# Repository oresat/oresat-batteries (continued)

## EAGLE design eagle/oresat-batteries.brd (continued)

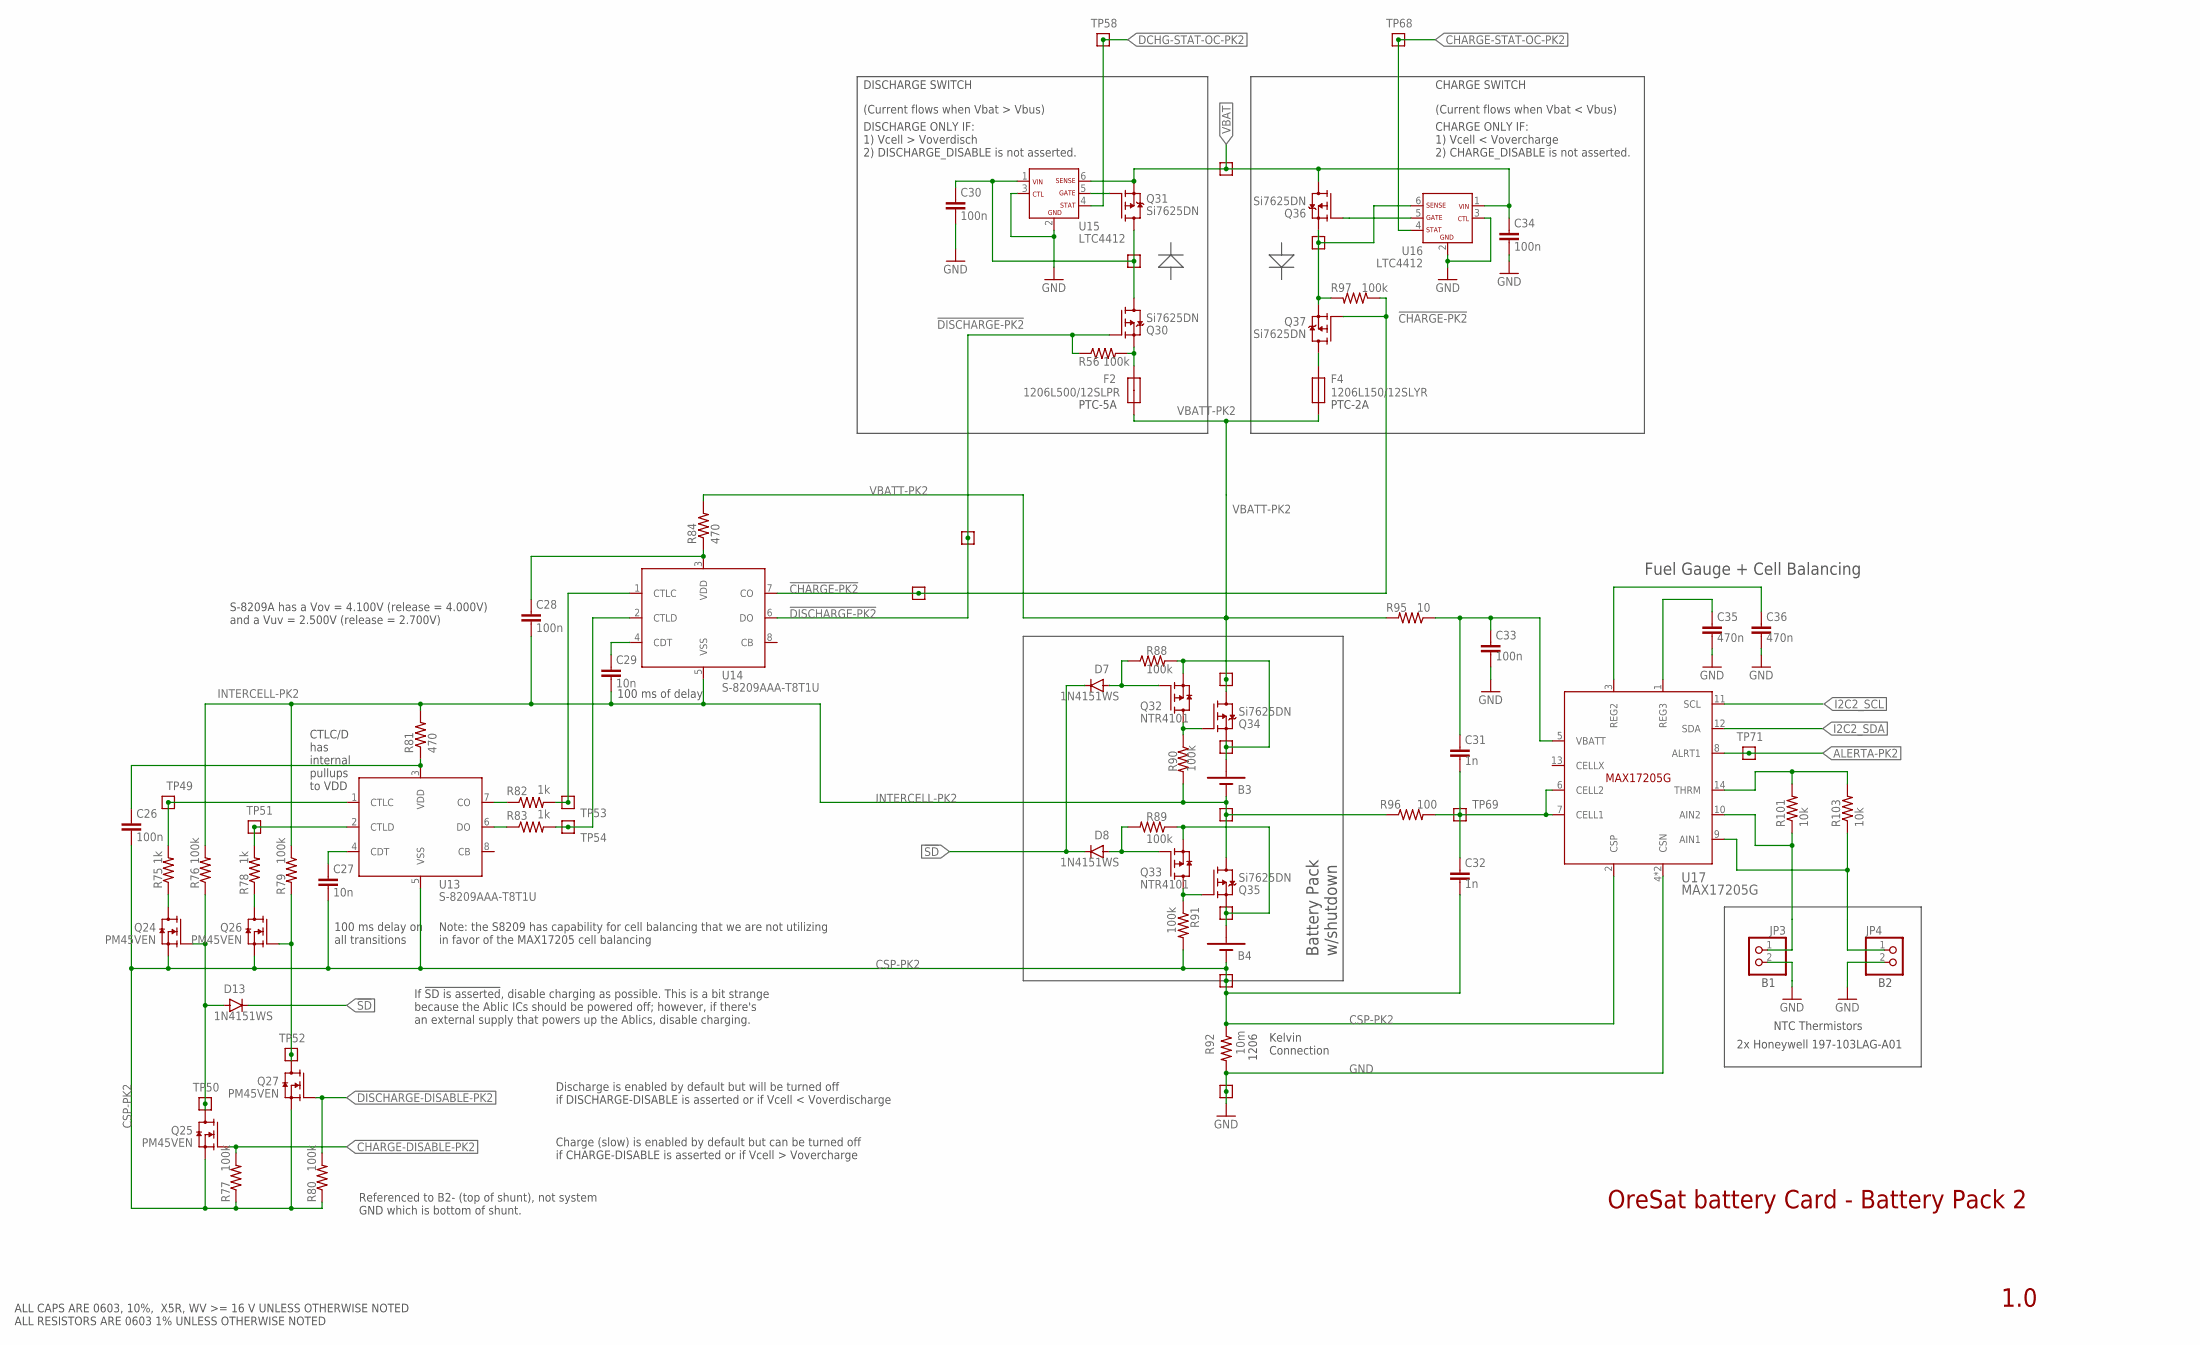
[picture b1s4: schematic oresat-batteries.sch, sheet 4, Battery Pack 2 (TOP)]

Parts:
B3, B4: B-18650-LI-BATTERY; 18650; MPN MH48285
C26, C28, C30, C33, C34: 100n; .0603-C-NOSILK; MPN C0603C104M4RACTU
C27, C29: 10n; .0603-C-NOSILK; MPN C0603C103M5RACTU
C31, C32: 1n; .0603-C-NOSILK; MPN CC0603KRX7R9BB102
C35, C36: 470n; .0603-C-NOSILK; MPN C0603C474K4PACTU
D7, D8, D13: 1N4151WS; SOD323-R; MPN 1N4151WS-E3-08
F2: 1206L500/12SLPR; 1206-C; MPN NANOSMD350LR-C-2
F4: 1206L150/12SLYR; 1206-C; MPN NANOSMD350LR-C-2
JP3, JP4: PINHD-1X2; 1X02
Q24, Q25, Q26, Q27: PM45VEN; SOT23-3; MPN PMV45EN2R
Q30, Q31, Q34, Q35, Q36, Q37: Si7625DN; POWERPAK-1212-8; MPN SI7625DN-T1-GE3
Q32, Q33: NTR4101; SOT23-3; MPN NTR4101PT1G
R56, R97: 100k; .0603-C-NOSILK; MPN RR0816P-104-D
R75, R78, R82, R83: 1k; .0603-C-NOSILK; MPN RC0603JR-071KL
R76, R79, R88, R89, R90, R91: 100k; .0603-C-NOSILK; MPN RC0603FR-071ML
R77, R80: 100k; .0603-C-NOSILK; MPN RC0603FR-0710KL
R81, R84: 470; .0603-C-NOSILK; MPN RC0603JR-07470RL
R92: 10m; 1206-C; MPN CSR1206-0R01F1
R95: 10; .0603-C-NOSILK; MPN RC0603FR-0710RL
R96: 100; .0603-C-NOSILK; MPN RC0603FR-07100RL
R101, R103: 10k; .0603-C-NOSILK; MPN RC0603FR-0710KL
TP24, TP49, TP50, TP51, TP52, TP53, TP54, TP55, TP56, TP58, TP59, TP61, TP62, TP63, TP64, TP65, TP66, TP67, TP68, TP69, TP71: TEST-POINT-LARGE-SQUARE; 1X01
U13, U14: S-8209AAA-T8T1U; TSSOP8; MPN S-8209AAA-T8T1U
U15, U16: LTC4412; SOT23-6; MPN LTC4412ES6#TRPBF
U17: MAX17205G; 21-0137I_T1433-2; MPN MAX17205G+T

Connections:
!CHARGE-PK2: Q37.4 (G), R97.1, TP56.1, U14.7 (CO)
!DISCHARGE-PK2: Q30.4 (G), R56.1, TP55.1, U14.6 (DO)
!SD: D7.C, D8.C, D13.C; also elsewhere on the board
AIN1-PK2: JP4.1, R103.1, U17.9 (AIN1)
AIN2-PK2: JP3.1, R101.1, U17.10 (AIN2)
ALERTA-PK2: TP71.1, U17.8 (ALRT1); also elsewhere on the board
CELL1-PK2: C31.2, C32.1, R96.2, TP69.1, U17.6 (CELL2), U17.7 (CELL1)
CHARGE-DISABLE-PK2: Q25.1 (G), R77.2; also elsewhere on the board
CHARGE-STAT-OC-PK2: TP68.1, U16.4 (STAT); also elsewhere on the board
CSP-PK2: B4.NEG-T (NEG), C26.2, C27.2, C32.2, Q24.2 (S), Q25.2 (S), Q26.2 (S), Q27.2 (S), R77.1, R80.1, R91.2, R92.1, TP65.1, U13.5 (VSS), U17.2 (CSP)
DCHG-STAT-OC-PK2: TP58.1, U15.4 (STAT); also elsewhere on the board
DISCHARGE-DISABLE-PK2: Q27.1 (G), R80.2; also elsewhere on the board
GND: C30.2, C33.2, C34.2, C35.2, C36.2, JP3.2, JP4.2, R92.2, TP66.1, U15.2 (GND), U15.3 (CTL), U16.2 (GND), U16.3 (CTL), U17.4 (CSN), U17.EP (CSN); also elsewhere on the board
I2C2_SCL: U17.11 (SCL); also elsewhere on the board
I2C2_SDA: U17.12 (SDA); also elsewhere on the board
INTERCELL-PK2: B3.NEG-T (NEG), C28.2, C29.2, Q35.5 (D), Q35.6 (D), Q35.7 (D), Q35.8 (D), Q35.PAD (D), R76.2, R79.1, R81.2, R90.2, R96.1, TP63.1, U14.5 (VSS)
unnamed: F4.1, Q37.5 (D), Q37.6 (D), Q37.7 (D), Q37.8 (D), Q37.PAD (D)
unnamed: Q36.1 (S), Q36.2 (S), Q36.3 (S), Q37.1 (S), Q37.2 (S), Q37.3 (S), R97.2, TP67.1, U16.6 (SENSE)
unnamed: F2.1, Q30.1 (S), Q30.2 (S), Q30.3 (S), R56.2
unnamed: R83.1, U13.6 (DO)
unnamed: R82.1, U13.7 (CO)
unnamed: R83.2, TP54.1, U14.2 (CTLD)
unnamed: R82.2, TP53.1, U14.1 (CTLC)
unnamed: R75.2, TP49.1, U13.1 (CTLC)
unnamed: C28.1, R84.1, U14.3 (VDD)
unnamed: C26.1, R81.1, U13.3 (VDD)
unnamed: C29.1, U14.4 (CDT)
unnamed: C27.1, U13.4 (CDT)
unnamed: Q31.4 (G), U15.5 (GATE)
unnamed: Q26.1 (G), Q27.3 (D), R79.2, TP52.1
unnamed: R78.2, TP51.1, U13.2 (CTLD)
unnamed: Q26.3 (D), R78.1
unnamed: Q36.4 (G), U16.5 (GATE)
unnamed: B3.POS-T (POS), Q32.2 (S), Q34.1 (S), Q34.2 (S), Q34.3 (S), R88.2, TP62.1
unnamed: Q33.3 (D), Q35.4 (G), R91.1
unnamed: D8.A, Q33.1 (G), R89.2
unnamed: B4.POS-T (POS), Q33.2 (S), Q35.1 (S), Q35.2 (S), Q35.3 (S), R89.1, TP64.1
unnamed: Q32.3 (D), Q34.4 (G), R90.1
unnamed: D7.A, Q32.1 (G), R88.1
unnamed: Q24.3 (D), R75.1
unnamed: D13.A, Q24.1 (G), Q25.3 (D), R76.1, TP50.1
REG2-PK2: C36.1, U17.3 (REG2)
REG3-PK2: C35.1, U17.1 (REG3)
THRM-PK2: R101.2, R103.2, U17.14 (THRM)
VBAT: C34.1, Q31.1 (S), Q31.2 (S), Q31.3 (S), Q36.5 (D), Q36.6 (D), Q36.7 (D), Q36.8 (D), Q36.PAD (D), TP59.1, U15.6 (SENSE), U16.1 (VIN); also elsewhere on the board
VBATT-F-PK2: C30.1, Q30.5 (D), Q30.6 (D), Q30.7 (D), Q30.8 (D), Q30.PAD (D), Q31.5 (D), Q31.6 (D), Q31.7 (D), Q31.8 (D), Q31.PAD (D), TP24.1, U15.1 (VIN)
VBATT-PK2: F2.2, F4.2, Q34.5 (D), Q34.6 (D), Q34.7 (D), Q34.8 (D), Q34.PAD (D), R84.2, R95.2, TP61.1
VBATT-PL2: C31.1, C33.1, R95.1, U17.5 (VBATT)

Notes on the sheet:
OreSat battery Card - Battery Pack 2
1.0
1206
NTC Thermistors
Battery Pack w/shutdown
Fuel Gauge + Cell Balancing
Note: the S8209 has capability for cell balancing that we are not utilizing in favor of the MAX17205 cell balancing
100 ms of delay
DISCHARGE SWITCH
(Current flows when Vbat > Vbus)
DISCHARGE ONLY IF: 1) Vcell > Voverdisch 2) DISCHARGE_DISABLE is not asserted.
CTLC/D has internal pullups to VDD
100 ms delay on all transitions
Discharge is enabled by default but will be turned off if DISCHARGE-DISABLE is asserted or if Vcell < Voverdischarge
Charge (slow) is enabled by default but can be turned off if CHARGE-DISABLE is asserted or if Vcell > Vovercharge
CHARGE SWITCH
(Current flows when Vbat < Vbus)
CHARGE ONLY IF: 1) Vcell < Vovercharge 2) CHARGE_DISABLE is not asserted.
Kelvin Connection
S-8209A has a Vov = 4.100V (release = 4.000V) and a Vuv = 2.500V (release = 2.700V)
Referenced to B2- (top of shunt), not system GND which is bottom of shunt.
ALL CAPS ARE 0603, 10%, X5R, WV >= 16 V UNLESS OTHERWISE NOTED ALL RESISTORS ARE 0603 1% UNLESS OTHERWISE NOTED
PTC-5A
PTC-2A
2x Honeywell 197-103LAG-A01
If !SD is asserted, disable charging as possible. This is a bit strange because the Ablic ICs should be powered off; however, if there's an external supply that powers up the Ablics, disable charging.

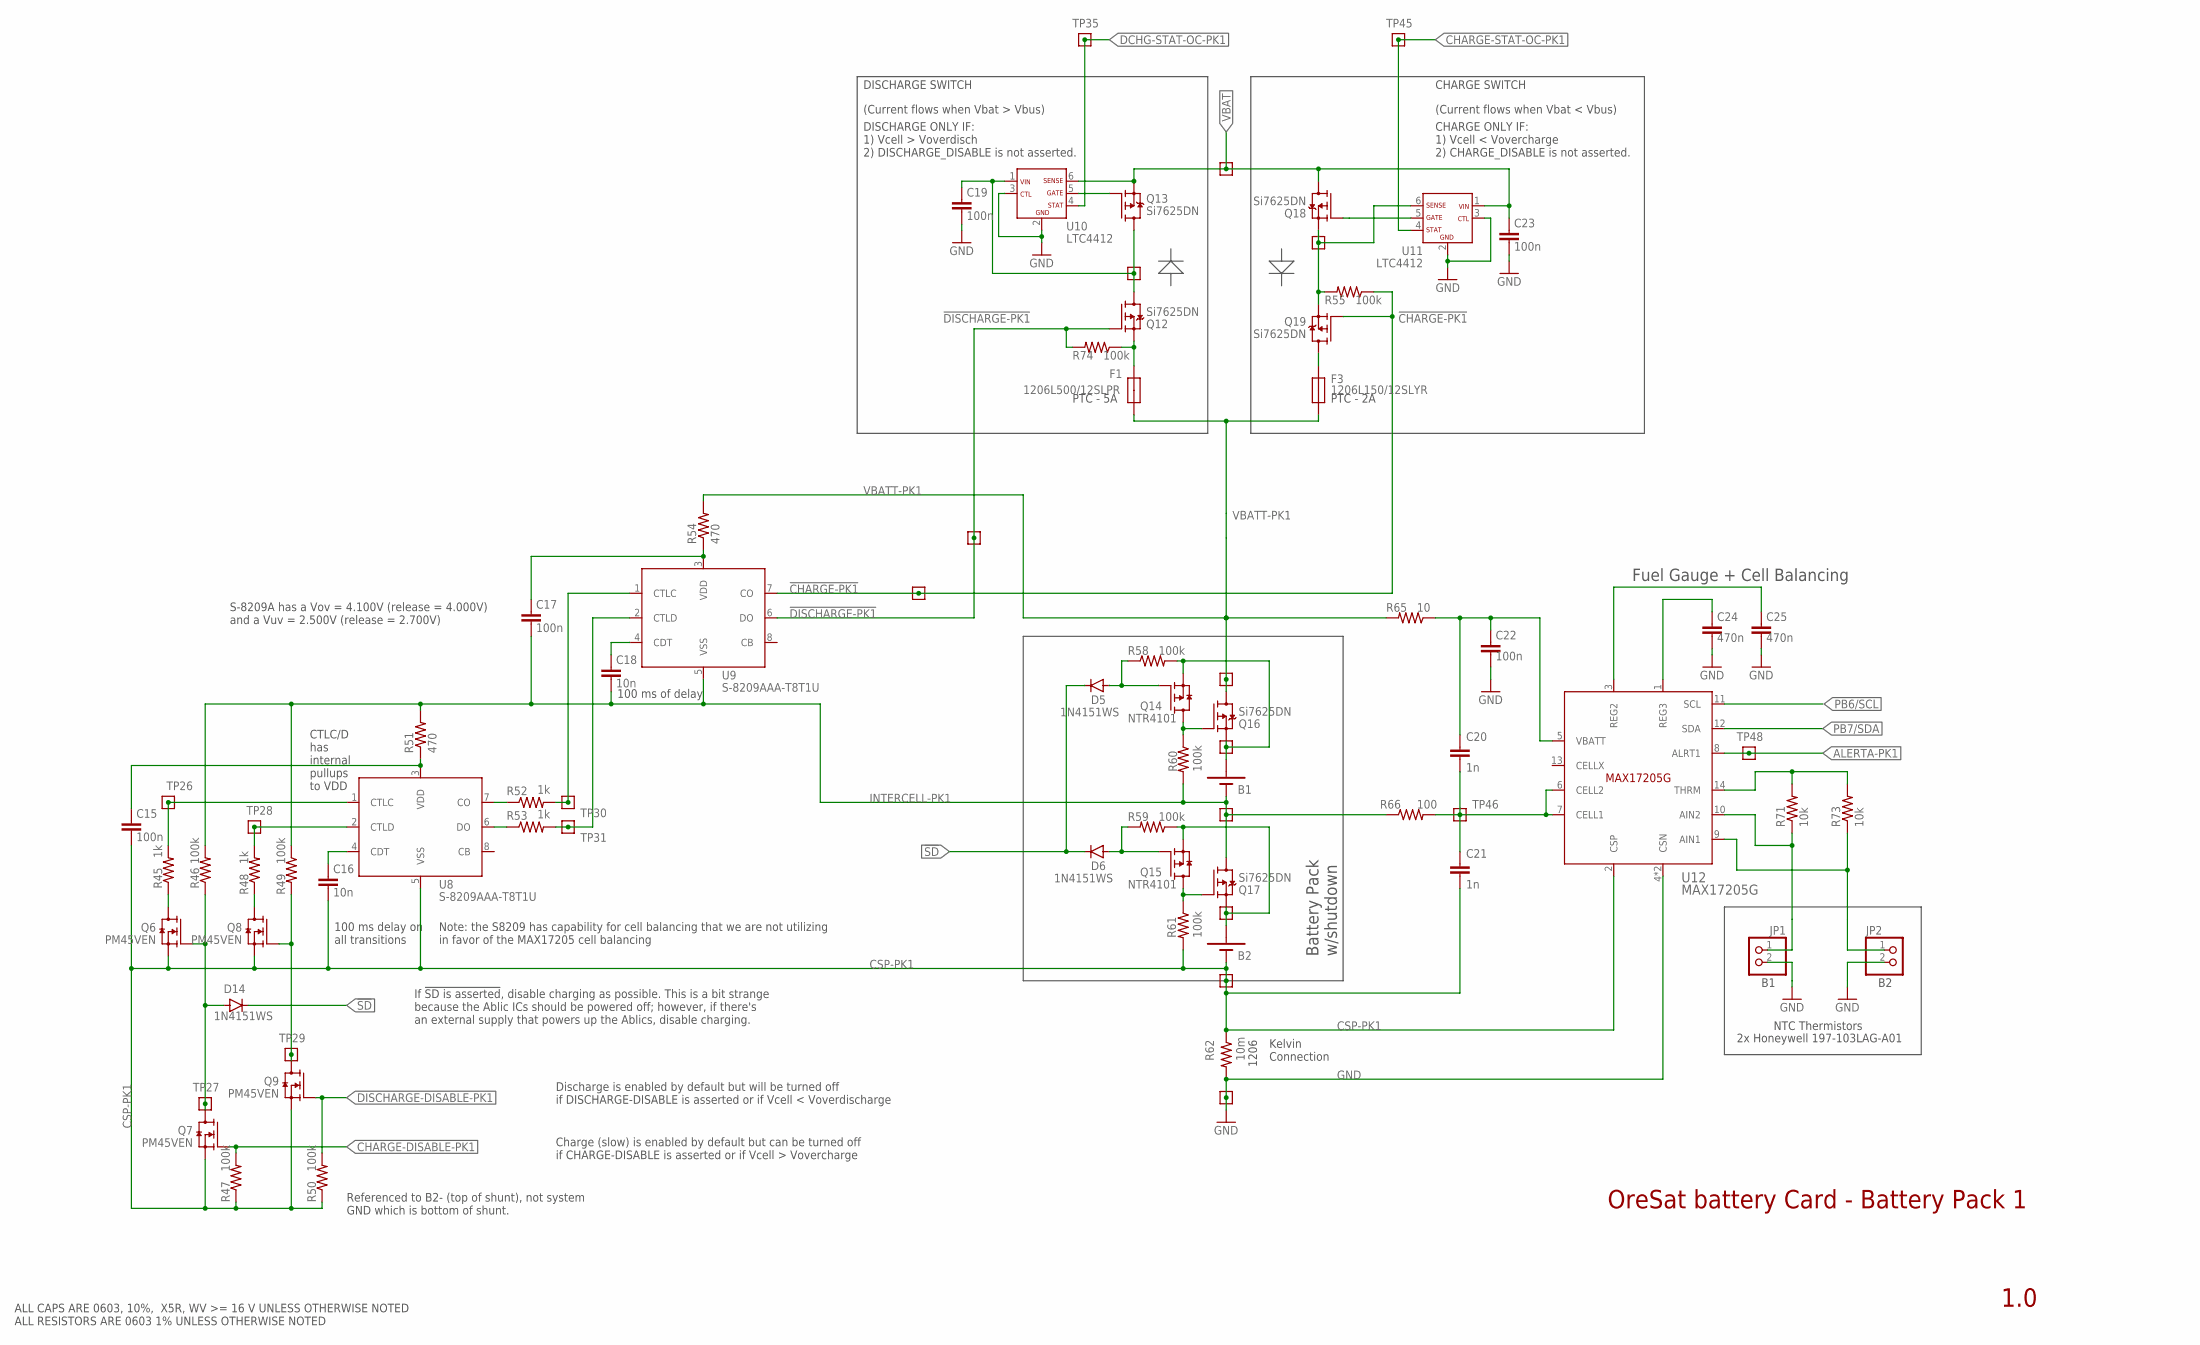
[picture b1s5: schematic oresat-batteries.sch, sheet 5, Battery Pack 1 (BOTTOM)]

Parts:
B1, B2: B-18650-LI-BATTERY; 18650; MPN MH48285
C15, C17, C19, C22, C23: 100n; .0603-C-NOSILK; MPN C0603C104M4RACTU
C16, C18: 10n; .0603-C-NOSILK; MPN C0603C103M5RACTU
C20, C21: 1n; .0603-C-NOSILK; MPN CC0603KRX7R9BB102
C24, C25: 470n; .0603-C-NOSILK; MPN C0603C474K4PACTU
D5, D6, D14: 1N4151WS; SOD323-R; MPN 1N4151WS-E3-08
F1: 1206L500/12SLPR; 1206-C; MPN NANOSMD350LR-C-2
F3: 1206L150/12SLYR; 1206-C; MPN NANOSMD350LR-C-2
JP1, JP2: PINHD-1X2; 1X02
Q6, Q7, Q8, Q9: PM45VEN; SOT23-3; MPN PMV45EN2R
Q12, Q13, Q16, Q17, Q18, Q19: Si7625DN; POWERPAK-1212-8; MPN SI7625DN-T1-GE3
Q14, Q15: NTR4101; SOT23-3; MPN NTR4101PT1G
R45, R48, R52, R53: 1k; .0603-C-NOSILK; MPN 311-1.0KGRCT-ND
R46, R49, R58, R59, R60, R61: 100k; .0603-C-NOSILK; MPN RC0603FR-071ML
R47, R50: 100k; .0603-C-NOSILK; MPN RC0603FR-0710KL
R51, R54: 470; .0603-C-NOSILK; MPN RC0603JR-07470RL
R55, R74: 100k; .0603-C-NOSILK; MPN RR0816P-104-D
R62: 10m; 1206-C; MPN CSR1206-0R01F1
R65: 10; .0603-C-NOSILK; MPN RC0603FR-0710RL
R66: 100; .0603-C-NOSILK; MPN RC0603FR-07100RL
R71, R73: 10k; .0603-C-NOSILK; MPN RC0603FR-0710KL
TP23, TP26, TP27, TP28, TP29, TP30, TP31, TP32, TP33, TP35, TP36, TP38, TP39, TP40, TP41, TP42, TP43, TP44, TP45, TP46, TP48: TEST-POINT-LARGE-SQUARE; 1X01
U8, U9: S-8209AAA-T8T1U; TSSOP8; MPN S-8209AAA-T8T1U
U10, U11: LTC4412; SOT23-6; MPN LTC4412ES6#TRPBF
U12: MAX17205G; 21-0137I_T1433-2; MPN MAX17205G+T

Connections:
!CHARGE-PK1: Q19.4 (G), R55.1, TP33.1, U9.7 (CO)
!DISCHARGE-PK1: Q12.4 (G), R74.2, TP32.1, U9.6 (DO)
!SD: D5.C, D6.C, D14.C; also elsewhere on the board
AIN1-PK1: JP2.1, R73.1, U12.9 (AIN1)
AIN2-PK1: JP1.1, R71.1, U12.10 (AIN2)
ALERTA-PK1: TP48.1, U12.8 (ALRT1); also elsewhere on the board
CELL1-PK1: C20.2, C21.1, R66.2, TP46.1, U12.6 (CELL2), U12.7 (CELL1)
CHARGE-DISABLE-PK1: Q7.1 (G), R47.2; also elsewhere on the board
CHARGE-STAT-OC-PK1: TP45.1, U11.4 (STAT); also elsewhere on the board
CSP-PK1: B2.NEG-T (NEG), C15.2, C16.2, C21.2, Q6.2 (S), Q7.2 (S), Q8.2 (S), Q9.2 (S), R47.1, R50.1, R61.2, R62.1, TP42.1, U8.5 (VSS), U12.2 (CSP)
DCHG-STAT-OC-PK1: TP35.1, U10.4 (STAT); also elsewhere on the board
DISCHARGE-DISABLE-PK1: Q9.1 (G), R50.2; also elsewhere on the board
GND: C19.2, C22.2, C23.2, C24.2, C25.2, JP1.2, JP2.2, R62.2, TP43.1, U10.2 (GND), U10.3 (CTL), U11.2 (GND), U11.3 (CTL), U12.4 (CSN), U12.EP (CSN); also elsewhere on the board
INTERCELL-PK1: B1.NEG-T (NEG), C17.2, C18.2, Q17.5 (D), Q17.6 (D), Q17.7 (D), Q17.8 (D), Q17.PAD (D), R46.2, R49.1, R51.2, R60.2, R66.1, TP40.1, U9.5 (VSS)
unnamed: R53.2, TP31.1, U9.2 (CTLD)
unnamed: R53.1, U8.6 (DO)
unnamed: R52.2, TP30.1, U9.1 (CTLC)
unnamed: Q8.3 (D), R48.1
unnamed: R52.1, U8.7 (CO)
unnamed: C16.1, U8.4 (CDT)
unnamed: Q13.4 (G), U10.5 (GATE)
unnamed: Q6.3 (D), R45.1
unnamed: Q8.1 (G), Q9.3 (D), R49.2, TP29.1
unnamed: C18.1, U9.4 (CDT)
unnamed: R45.2, TP26.1, U8.1 (CTLC)
unnamed: Q14.3 (D), Q16.4 (G), R60.1
unnamed: C17.1, R54.1, U9.3 (VDD)
unnamed: C15.1, R51.1, U8.3 (VDD)
unnamed: R48.2, TP28.1, U8.2 (CTLD)
unnamed: D6.A, Q15.1 (G), R59.2
unnamed: B1.POS-T (POS), Q14.2 (S), Q16.1 (S), Q16.2 (S), Q16.3 (S), R58.2, TP39.1
unnamed: Q18.4 (G), U11.5 (GATE)
unnamed: Q15.3 (D), Q17.4 (G), R61.1
unnamed: F3.1, Q19.5 (D), Q19.6 (D), Q19.7 (D), Q19.8 (D), Q19.PAD (D)
unnamed: D5.A, Q14.1 (G), R58.1
unnamed: D14.A, Q6.1 (G), Q7.3 (D), R46.1, TP27.1
unnamed: B2.POS-T (POS), Q15.2 (S), Q17.1 (S), Q17.2 (S), Q17.3 (S), R59.1, TP41.1
unnamed: F1.1, Q12.1 (S), Q12.2 (S), Q12.3 (S), R74.1
unnamed: Q18.1 (S), Q18.2 (S), Q18.3 (S), Q19.1 (S), Q19.2 (S), Q19.3 (S), R55.2, TP44.1, U11.6 (SENSE)
PB6/SCL: U12.11 (SCL); also elsewhere on the board
PB7/SDA: U12.12 (SDA); also elsewhere on the board
REG2-PK1: C25.1, U12.3 (REG2)
REG3-PK1: C24.1, U12.1 (REG3)
THRM-PK1: R71.2, R73.2, U12.14 (THRM)
VBAT: C23.1, Q13.1 (S), Q13.2 (S), Q13.3 (S), Q18.5 (D), Q18.6 (D), Q18.7 (D), Q18.8 (D), Q18.PAD (D), TP36.1, U10.6 (SENSE), U11.1 (VIN); also elsewhere on the board
VBATT-F-PK1: C19.1, Q12.5 (D), Q12.6 (D), Q12.7 (D), Q12.8 (D), Q12.PAD (D), Q13.5 (D), Q13.6 (D), Q13.7 (D), Q13.8 (D), Q13.PAD (D), TP23.1, U10.1 (VIN)
VBATT-PK1: F1.2, F3.2, Q16.5 (D), Q16.6 (D), Q16.7 (D), Q16.8 (D), Q16.PAD (D), R54.2, R65.2, TP38.1
VBATT-PL1: C20.1, C22.1, R65.1, U12.5 (VBATT)

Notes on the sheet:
1206
NTC Thermistors
Battery Pack w/shutdown
Fuel Gauge + Cell Balancing
Note: the S8209 has capability for cell balancing that we are not utilizing in favor of the MAX17205 cell balancing
100 ms of delay
DISCHARGE SWITCH
(Current flows when Vbat > Vbus)
DISCHARGE ONLY IF: 1) Vcell > Voverdisch 2) DISCHARGE_DISABLE is not asserted.
CTLC/D has internal pullups to VDD
100 ms delay on all transitions
Discharge is enabled by default but will be turned off if DISCHARGE-DISABLE is asserted or if Vcell < Voverdischarge
Charge (slow) is enabled by default but can be turned off if CHARGE-DISABLE is asserted or if Vcell > Vovercharge
CHARGE SWITCH
(Current flows when Vbat < Vbus)
CHARGE ONLY IF: 1) Vcell < Vovercharge 2) CHARGE_DISABLE is not asserted.
OreSat battery Card - Battery Pack 1
1.0
Kelvin Connection
S-8209A has a Vov = 4.100V (release = 4.000V) and a Vuv = 2.500V (release = 2.700V)
Referenced to B2- (top of shunt), not system GND which is bottom of shunt.
ALL CAPS ARE 0603, 10%, X5R, WV >= 16 V UNLESS OTHERWISE NOTED ALL RESISTORS ARE 0603 1% UNLESS OTHERWISE NOTED
PTC - 5A
PTC - 2A
2x Honeywell 197-103LAG-A01
If !SD is asserted, disable charging as possible. This is a bit strange because the Ablic ICs should be powered off; however, if there's an external supply that powers up the Ablics, disable charging.

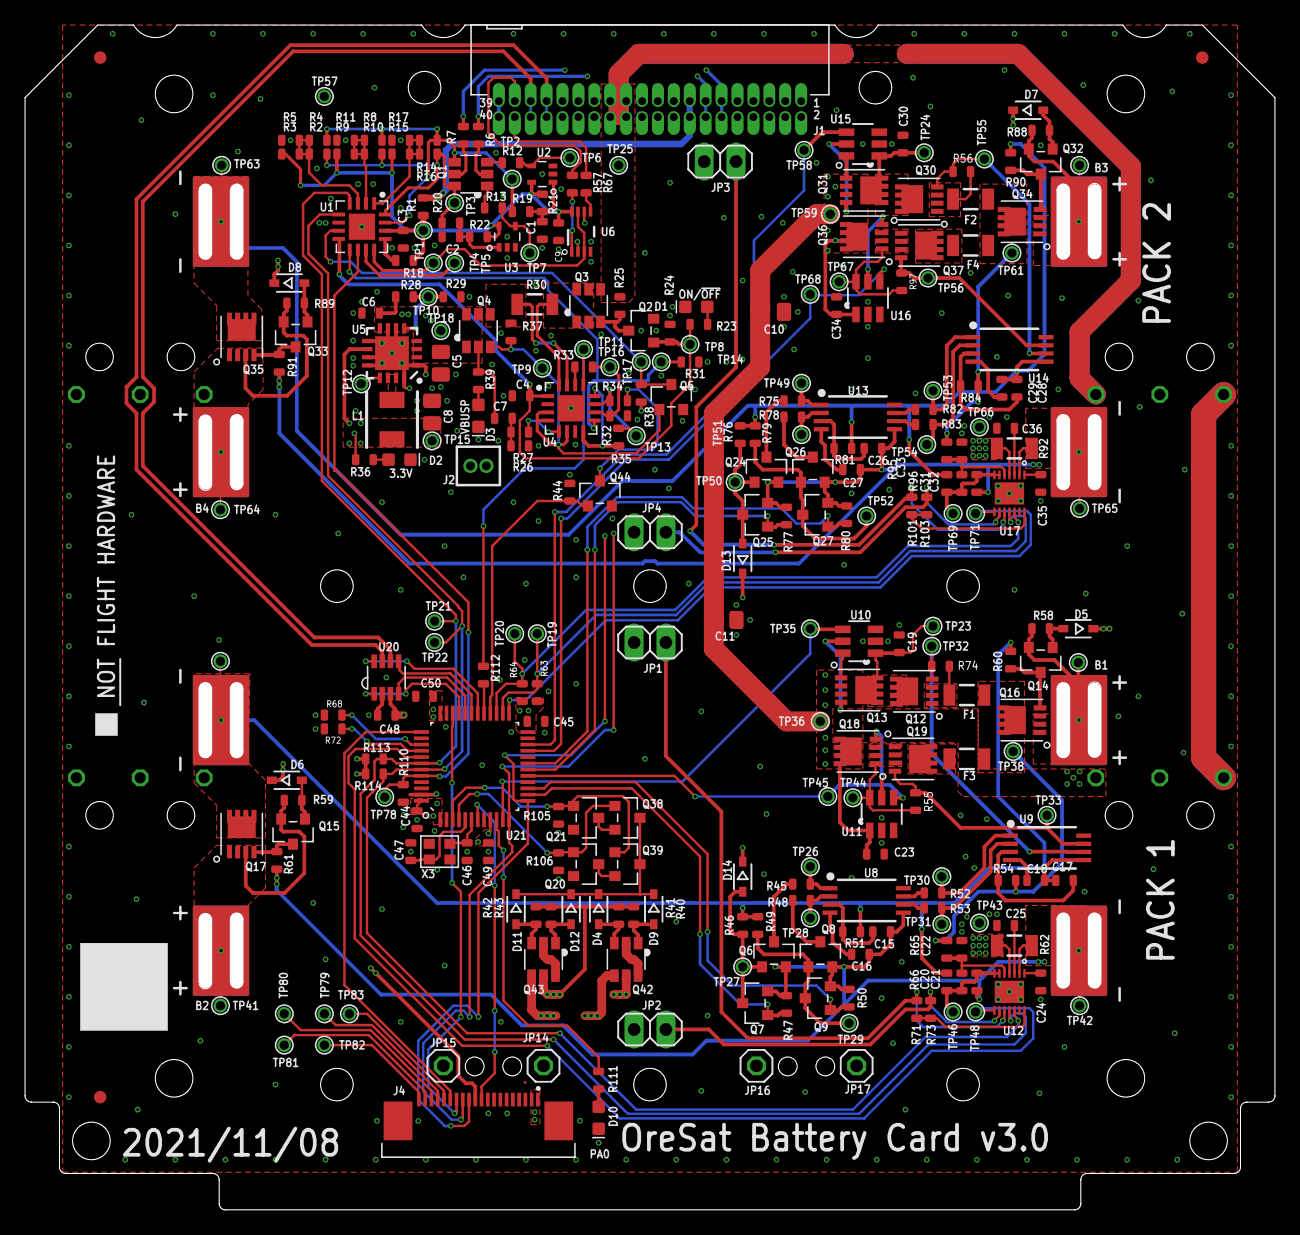
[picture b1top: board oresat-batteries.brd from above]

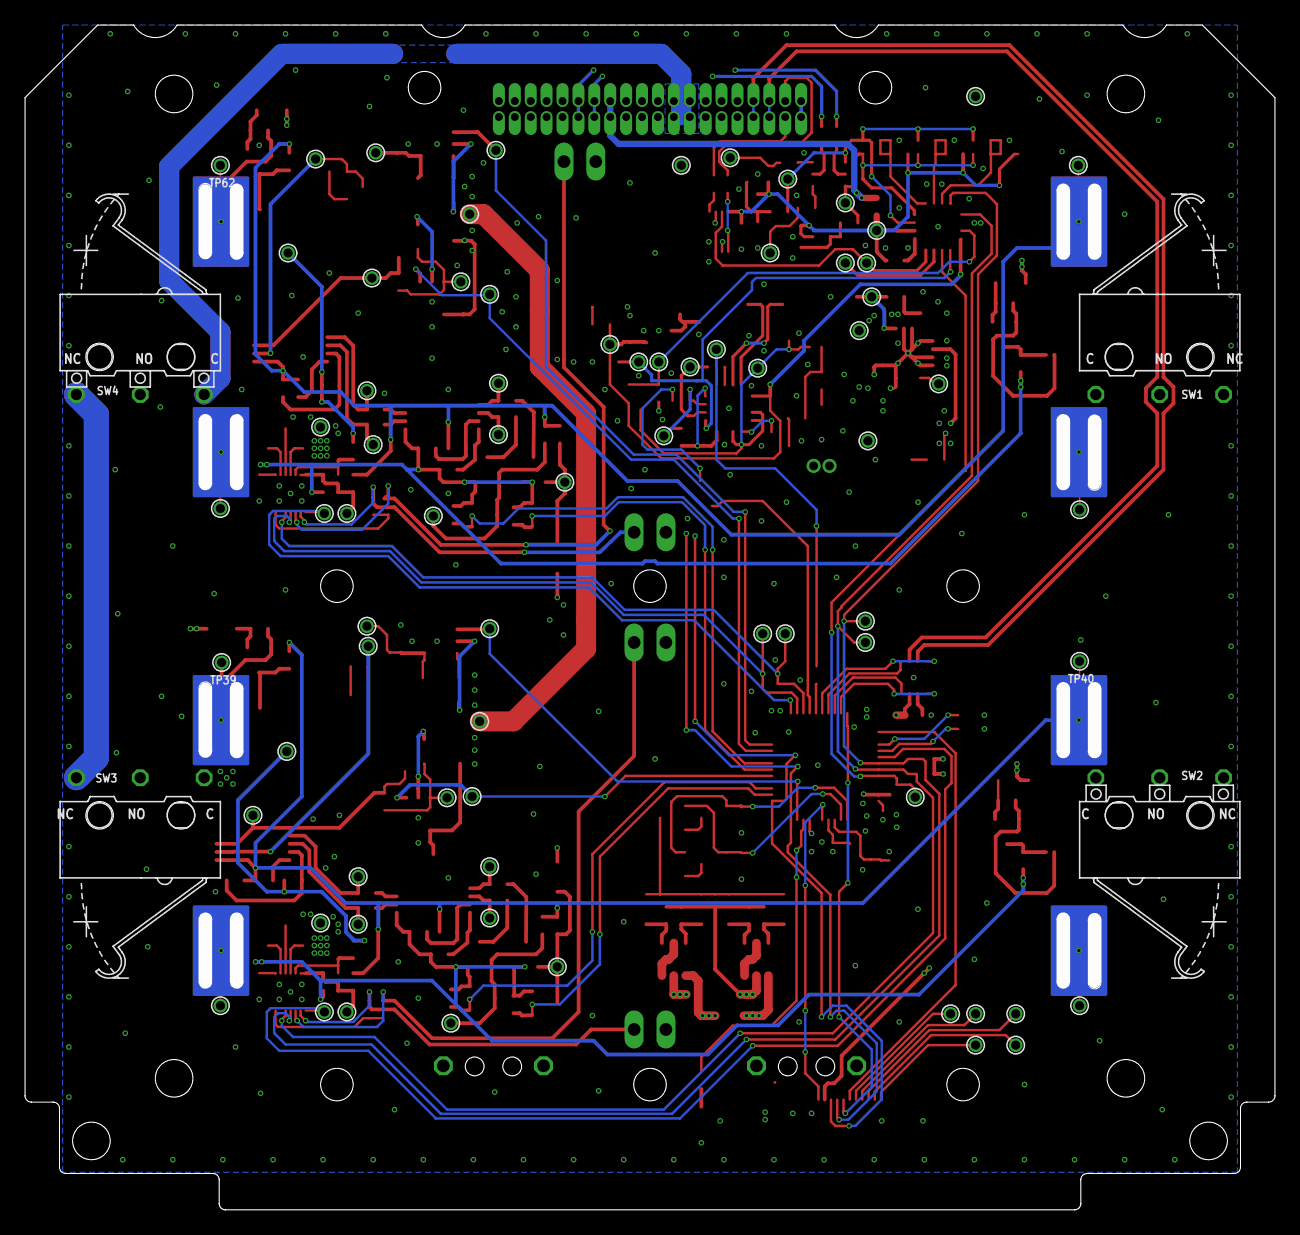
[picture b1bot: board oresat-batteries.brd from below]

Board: 4 copper layers, 99.8 x 94.6 mm, 309 parts (4 on the bottom side), 179 nets.

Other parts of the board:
U$2: ORESAT-CARD-V1.3-BATTERY-V3.0

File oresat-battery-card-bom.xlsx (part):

OreSat Battery Board v3
Qty | Parts | MFR | MPN | Description | Assembly | STOCK | DIST | DPN | DIST2 | DPN2
4 | B1, B2, B3, B4 | Tenergy | MH48285 | 2600 mAh 18650 Li-Po (w/ tabs) | TH | 39 | Tenergy | MH48285
2 | C46, C47 | KEMET | C0603C200J5GACAUTO | 20pF ±5% 50V Ceramic Capacitor C0G, NP0 0603 (1608 Metric) |  | 25 | Digi-Key | 399-15921-1-ND
4 | C20, C21, C31, C32 | KEMET | C0603C102J3RACAUTO | 1000pF ±5% 25V Ceramic Capacitor X7R 0603 (1608 Metric) |  | 175 | Digi-Key | 399-C0603C102J3RACAUTOCT-ND
4 | C16, C18, C27, C29 | KEMET | C0603C103J3GECAUTO | 10000pF ±10% 50V Ceramic Capacitor X7R 0603 (1608 Metric) |  | 160 | Digi-Key | 399-14102-1-ND
17 | C3, C9, C15, C17, C19, C22, C23, C26, C28, C30, C33, C34, C44, C45, C48, C49, C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 | Taiyo Yuden | TMK107BJ104KAHT | 0.1µF ±10% 25V Ceramic Capacitor X5R 0603 (1608 Metric) |  | 40 | Digi-Key | 587-3472-1-ND
4 | C24, C25, C35, C36 | Taiyo Yuden | TMK107BJ474KAHT | 0.47 µF ±10% 25V Ceramic Capacitor X5R 0603 (1608 Metric) |  | 160 | Digi-Key | 587-3476-1-ND
5 | C1, C2, C4, C6, C7 | Taiyo Yuden | TMK107BJ105KAHT | 1µF ±10% 25V Ceramic Capacitor X5R 0603 (1608 Metric) |  | 5 | Digi-Key | 587-3473-1-ND
3 | C5, C10, C11 | Taiyo Yuden | TMK212BBJ106KGHT | 10µF ±10% 25V Ceramic Capacitor X5R 0805 (2012 Metric) |  | 40 | Digi-Key | 587-4334-1-ND
1 | C8 | Murata Electronics | GRT21BR61C226ME13L | 22µF ±20% 16V Ceramic Capacitor X5R 0805 (2012 Metric) |  | 20 | Digi-Key | 490-12383-1-ND
1 | D10 | Inolux | IN-S63AT5A | Amber 605nm LED Indication - Discrete 1.9V 0603 (1608 Metric) |  | 35 | Digi-Key | 1830-1064-1-ND
3 | D1, D2, D3 | Rohm | SML-E12M8WT86 | Green 572nm LED Indication - Discrete 2.2V 0603 (1608 Metric) |  | 3 | Digi-Key | 511-1584-1-ND
10 | D4, D5, D6, D7, D8, D9, D11, D12, D13, D14 | Vishay | 1N4151WS-E3-08 | Diode Standard 50V 150mA Surface Mount SOD-323 |  | 207 | Digi-Key | 112-1N4151WS-E3-08CT-ND
2 | F1, F2 | Littelfuse Inc. | 1206L500/12SLPR | Polymeric PTC Resettable Fuse 12V 5A Ih Surface Mount 1206 (3216 Metric), Conca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 |  | 12 | Digi-Key | 18-1206L500/12SLPRCT-ND
2 | F3, F4 | Littelfuse Inc. | 1206L150/12SLYR | Polymeric PTC Resettable Fuse 12V 1.5A Ih Surface Mount 1206 (3216 Metric), Con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 |  | 12 | Digi-Key | F5765CT-ND
2 | H1, H2 | Minco | HK6903 | Polyimide Thermofoil™ Heater, Acrylic PSA, 4.0 x 0.5 inches, 28V, 16 W, 48.91 o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 | TH | 0 | Minco | HK6903
1 | J1 | Samtec | TFM-120-01-L-D-RA | Connector Header Through Hole, Right Angle 40 position 0.050" (1.27mm) | TH | 19 | Digi-Key | SAM10145-ND
1 | J2 | Samtec | FTS-101-01-L-D | Connector Header Through Hole 2 position 0.050" (1.27mm) | TH | 0 | Digi-Key | SAM1156-01-ND
1 | J4 | TE | 2-1734592-0 | 20 Position FPC Connector Contacts, Bottom 0.020" (0.50mm) Surface Mount, Right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 |  | 16 | Digi-Key | A100287CT-ND
1 | L1 | ECS | ECS-MPI4040R4-6R8-R | 6.8µH Shielded Inductor 2.4A 91mOhm Nonstandard |  | 32 | Digi-Key | XC2337CT-ND
3 | Q1, Q42, Q43 | Diodes Inc | DMP2240UDM-7 | Mosfet Array 2 P-Channel (Dual) 20V 2A 600mW Surface Mount SOT-26 |  | 25 | Digi-Key | DMP2240UDMDICT-ND
15 | Q2, Q5, Q6, Q7, Q8, Q9, Q20, Q21, Q24, Q25, Q26, Q27, Q38, Q39, Q44 | Nexperia | PMV45EN2R | N-Channel 30V 4.1A (Ta) 510mW (Ta), 5W (Tc) Surface Mount TO-236AB |  | 172 | Digi-Key | 1727-2307-1-ND
2 | Q3, Q4 | Diodes Inc | DMP3050LVT-7 | P-Channel 30V 4.5A (Ta) 1.8W (Ta) Surface Mount TSOT-26 |  | 28 | Digi-Key | DMP3050LVT-7DICT-ND
4 | Q14, Q15, Q32, Q33 | ON Semi | NTR4101PT1G | P-Channel 20V 1.8A (Ta) 420mW (Ta) Surface Mount SOT-23-3 (TO-236) |  | 103 | Digi-Key | NTR4101PT1GOSCT-ND
12 | Q12, Q13, Q16, Q17, Q18, Q19, Q30, Q31, Q34, Q35, Q36, Q37 | Vishay | SI7625DN-T1-GE3 | P-Channel 30V 35A (Tc) 3.7W (Ta), 52W (Tc) Surface Mount PowerPAK® 1212-8 |  | 81 | Digi-Key | SI7625DN-T1-GE3CT-ND
11 | R2, R3, R4, R8, R9, R10, R14, R15, R16, R29, R35 | DNS | DNS | DNS | DNS | -- | DNS | DNS
1 | R33 | Stackpole Electronics Inc | RMCF0603ZT0R00 | 0 Ohms Jumper 0.1W, 1/10W Chip Resistor 0603 (1608 Metric) Automotive AEC-Q200 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 |  | 200 | Digi-Key | RMCF0603ZT0R00CT-ND
2 | R62, R92 | Riedon | CSR1206-0R01F1 | 10 mOhms ±1% 1W Chip Resistor 1206 (3216 Metric) Current Sense, Non-Inductive M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 |  | 40 | Digi-Key | 696-1374-1-ND
1 | R30 | Stackpole Electronics Inc | CSR1206FTR100 | 100 mOhms ±1% 0.5W, 1/2W Chip Resistor 1206 (3216 Metric) Current Sense Thick F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 |  | 140 | Digi-Key | CSR1206FTR100CT-ND
3 | R1, R65, R95 | Stackpole Electronics Inc | RMCF0603FT10R0 | 10 Ohms ±1% 0.1W, 1/10W Chip Resistor 0603 (1608 Metric) Automotive AEC-Q200 Th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 |  | 200 | Digi-Key | RMCF0603FT10R0CT-ND
4 | R6, R7, R66, R96 | Stackpole Electronics Inc | RMCF0603FT100R | 100 Ohms ±1% 0.1W, 1/10W Chip Resistor 0603 (1608 Metric) Automotive AEC-Q200 T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 |  | 230 | Digi-Key | RMCF0603FT100RCT-ND
4 | R51, R54, R81, R84 | Stackpole Electronics Inc | RMCF0603FT470R | 470 Ohms ±1% 0.1W, 1/10W Chip Resistor 0603 (1608 Metric) Automotive AEC-Q200 T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 |  | 210 | Digi-Key | RMCF0603FT470RCT-ND
8 | R45, R48, R52, R53, R75, R78, R82, R83 | Stackpole Electronics Inc | RMCF0603FT1K00 | 1 kOhms ±1% 0.1W, 1/10W Chip Resistor 0603 (1608 Metric) Automotive AEC-Q200 Th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 |  | 270 | Digi-Key | RMCF0603FT1K00CT-ND
4 | R23, R36, R39, R111 | Stackpole Electronics Inc | RMCF0603FT2K70 | 2.7 kOhms ±1% 0.1W, 1/10W Chip Resistor 0603 (1608 Metric) Automotive AEC-Q200 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 |  | 200 | Digi-Key | RMCF0603FT2K70CT-ND
4 | R63, R64, R113, R114 | Stackpole Electronics Inc | RMCF0603FT4K70 | 4.7 kOhms ±1% 0.1W, 1/10W Chip Resistor 0603 (1608 Metric) Automotive AEC-Q200 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 |  | 100 | Digi-Key | RMCF0603FT4K70CT-ND
29 | R5, R11, R17, R18, R24, R25, R27, R28, R31, R32, R37, R38, R40, R41, R42, R43, 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 | Stackpole Electronics Inc | RMCF0603FT10K0 | 10 kOhms ±1% 0.1W, 1/10W Chip Resistor 0603 (1608 Metric) Automotive AEC-Q200 T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 |  | 1000 | Digi-Key | RMCF0603FT10K0CT-ND
1 | R34 | Stackpole Electronics Inc | RMCF0603FT20K0 | 20 kOhms ±1% 0.1W, 1/10W Chip Resistor 0603 (1608 Metric) Automotive AEC-Q200 T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 |  | 115 | Digi-Key | RMCF0603FT20K0CT-ND
21 | R26, R46, R47, R49, R50, R55, R56, R58, R59, R60, R61, R74, R76, R77, R79, R80,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 | Stackpole Electronics Inc | RMCF0603FT100K | 100 kOhms ±5% 0.1W, 1/10W Chip Resistor 0603 (1608 Metric) Automotive AEC-Q200 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 |  | 1000 | Digi-Key | RMCF0603FT100KCT-ND
2 | R19, R20 | Stackpole Electronics Inc | RMCF0603FT330K | 330 kOhms ±1% 0.1W, 1/10W Chip Resistor 0603 (1608 Metric) Automotive AEC-Q200 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 |  | 200 | Digi-Key | RMCF0603FT330KCT-ND
2 | R12, R13 | Stackpole Electronics Inc | RMCF0603FT665K | 665 kOhms ±1% 0.1W, 1/10W Chip Resistor 0603 (1608 Metric) Automotive AEC-Q200 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 |  | 190 | Digi-Key | RMCF0603FT665KCT-ND
2 | R21, R22 | Stackpole Electronics Inc | RMCF0603FT1M00 | 1 MOhms ±1% 0.1W, 1/10W Chip Resistor 0603 (1608 Metric) Automotive AEC-Q200 Th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 |  | 350 | Digi-Key | RMCF0603FT1M00CT-ND
4 | RT1, RT2, RT3, RT4 | Honeywell | 197-103LAG-A01 | NTC Thermistor 10k Bead | TH | 4 | Digi-Key | 480-5642-ND
4 | SW1, SW2, SW3, SW4 | Omron | D2F-5L3 | Switch SPDT Chassis Mount | TH | 12 | Digi-Key | SW1443-ND
1 | U1 | Maxim | MAX7310ATE+ | I/O Expander 8 I²C, SMBus 400kHz 16-TQFN (4x4) |  | 15 | Digi-Key | MAX7310ATE+-ND
2 | U2, U3 | Microchip | MIC842LYC5-TR | Comparator with Voltage Reference Push-Pull SC-70-5 |  | 23 | Digi-Key | 576-2927-1-ND
1 | U4 | Maxim | MAX4211FETE | Current Monitor Regulator High-Side 16-TQFN (4x4) |  | 30 | Digi-Key | MAX4211FETE+-ND
1 | U5 | Texas Instruments | TPS62111RSA | Buck Switching Regulator IC Positive Fixed 3.3V 1 Output 1.5A 16-VQFN Exposed P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 |  | 33 | Digi-Key | 296-37681-2-ND
1 | U6 | Texas Instruments | TS5A21366DCUR | 2 Circuit IC Switch 1:1 1Ohm 8-VSSOP |  | 0 | Digi-Key | 296-24304-1-ND
4 | U8, U9, U13, U14 | Ablic | S-8209AAA-T8T1U | Battery Multi-Function Controller IC Lithium Ion/Polymer 8-TSSOP |  | 18 | Digi-Key | S-8209AAA-T8T1U-ND
4 | U10, U11, U15, U16 | Analog Devices | LTC4412ES6#TRPBF | OR Controller Source Selector Switch P-Channel 2:1 TSOT-23-6 |  | 17 | Digi-Key | LTC4412ES6#TRPBFCT-ND
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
